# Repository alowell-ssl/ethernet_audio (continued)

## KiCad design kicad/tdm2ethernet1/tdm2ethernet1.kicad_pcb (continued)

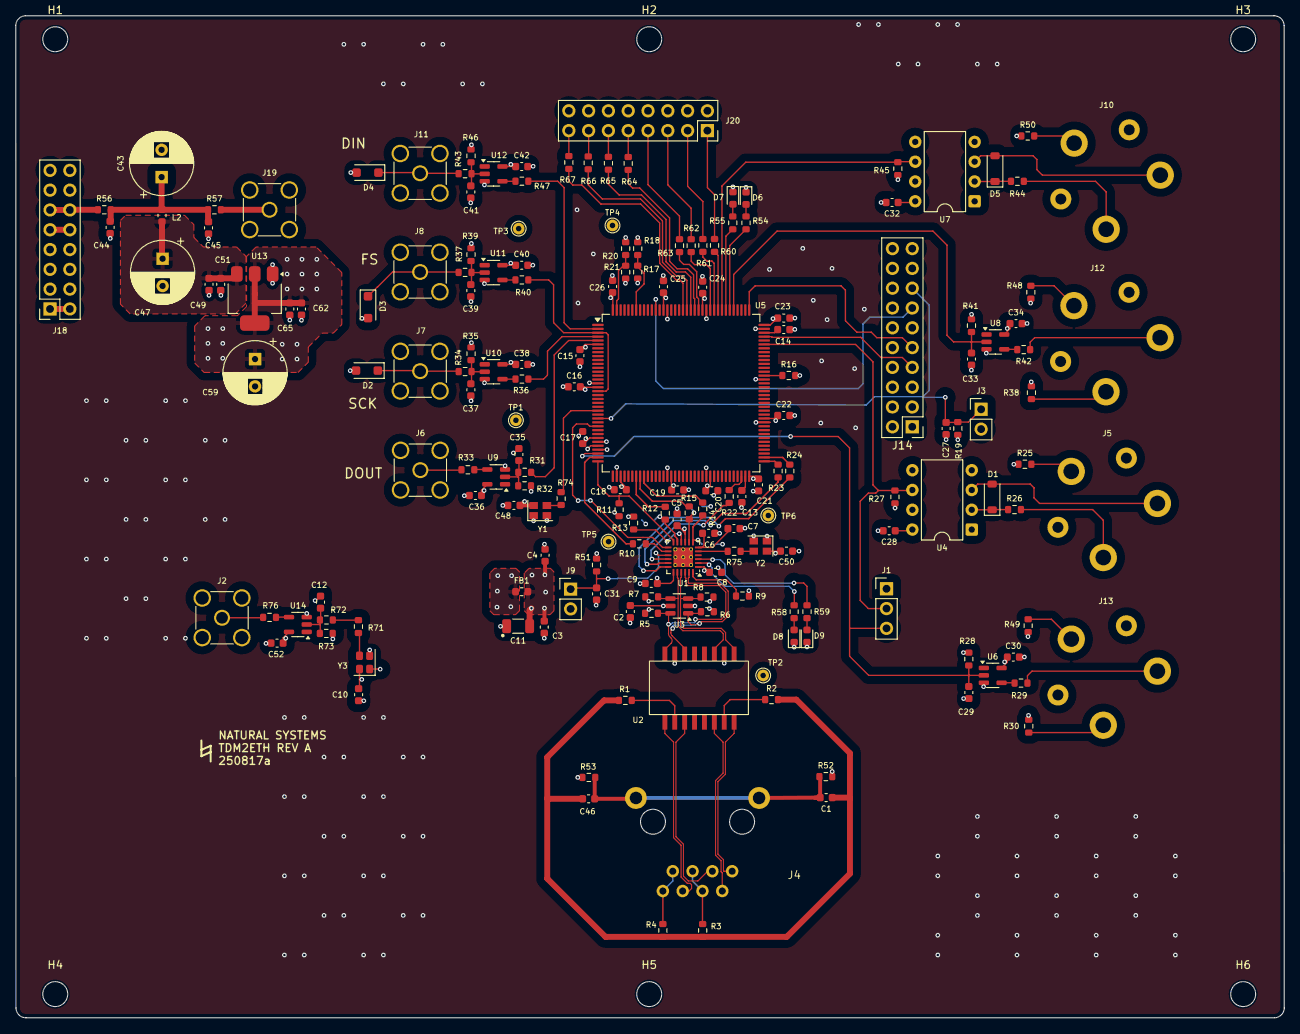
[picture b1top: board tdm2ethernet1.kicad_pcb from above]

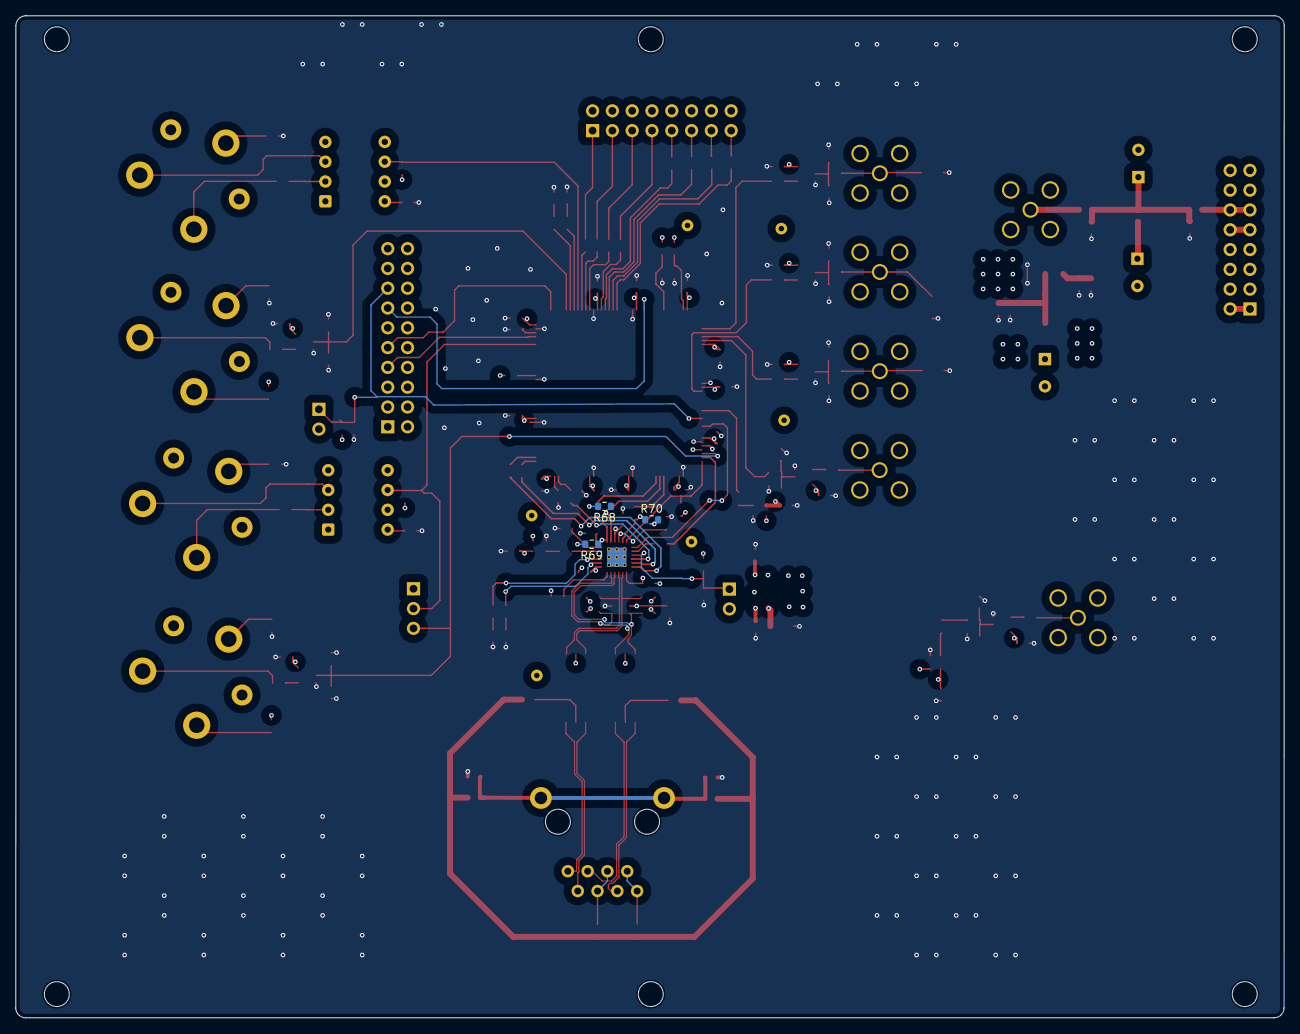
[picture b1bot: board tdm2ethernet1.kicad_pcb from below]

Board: 4 copper layers, 162.7 x 128.5 mm, 188 parts (3 on the bottom side), 121 nets.

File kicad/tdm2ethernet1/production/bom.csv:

Designator,Footprint,Quantity,Value,LCSC Part #
"C1, C46",0603,2,1nF,C1588
"C10, C16, C17, C18, C19, C2, C20, C21, C22, C23, C24, C25, C26, C27, C28, C3, C30, C31, C32, C34, C36, C38, C4, C40, C42, C45, C48, C5, C50, C51, C52, C62, C8, C9",0603,34,100nF,C14663
C11,1206,1,10uF,C13585
"C12, C29, C33, C35, C37, C39, C41",0603,7,C_Small,
"C13, C14",0603,2,2.2uF ceramic low ESR,C23630
"C15, C7",0603,2,1uF,C15849
"C43, C47, C59",CP_Radial_D8.0mm_P3.50mm,3,C_Polarized_Small,
"C44, C49, C65",0603,3,10uF,C96446
C6,0603,1,470pF,C1620
"D1, D5",D_SOD-123,2,1N4148W,C81598
"D2, D3, D4",D_SOD-123F,3,D_Zener_Small,
"D6, D7, D8, D9",0603,4,LED_Small,C2286
FB1,0603,1,600R @ 100 MHz,C1002
J1,PinHeader_1x03_P2.54mm_Vertical,1,Conn_01x03_Pin,
"J10, J12, J13, J5",Amphenol_ACJS,4,ACJS-MV35-3,
"J11, J19, J2, J6, J7, J8",SMA_Amphenol_901-144_Vertical,6,Conn_Coaxial,
J14,PinHeader_2x10_P2.54mm_Vertical,1,Conn_02x10_Odd_Even,
"J18, J20",PinSocket_2x08_P2.54mm_Vertical,2,Conn_02x08_Odd_Even,
"J3, J9",PinHeader_1x02_P2.54mm_Vertical,2,Conn_01x02_Pin,
J4,A-2014-2S-4-N-R,1,8P8C_Shielded,
L2,0603,1,L_Ferrite_Small,C1002
"R1, R2, R3, R4",0603,4,75,C4275
"R10, R12, R14, R15, R22, R23, R24, R29, R42, R71, R74, R75",0603,12,33,C23140
R11,0603,1,1.5k,C22843
"R13, R19, R51, R68, R69, R70",0603,6,10k,C15401
"R16, R17, R18, R20, R21, R25, R31, R34, R37, R43, R48, R49, R50, R52, R53, R56, R57, R60, R61, R62, R63, R64, R65, R66, R67, R72",0603,26,0,C21189
"R26, R44",0603,2,220,C22962
"R27, R45",0603,2,470,C23179
"R28, R32, R35, R39, R41, R46, R73",0603,7,R_Small,
"R30, R38",0603,2,2.2k,C4190
"R33, R36, R40, R47, R76",0603,5,22,C23345
"R5, R6, R7, R8",0603,4,49.9,C23185
"R54, R55, R58, R59",0603,4,4.7k,C23162
R9,0603,1,12.1k,C705723
"TP1, TP2, TP3, TP4, TP5, TP6",TestPoint_THTPad_D1.5mm_Drill0.7mm,6,TestPoint,
U1,VQFN-24-1EP_4x4mm_P0.5mm_EP2.5x2.5mm_ThermalVias,1,LAN8742A,C621424
"U10, U11, U12, U14, U6, U8, U9",SOT-23-5,7,74LVC1G17,C7836
U13,SOT-223,1,TLV1117-33,
U2,Untitled,1,KMS-1102NL,
U3,SOT-23-6,1,USBLC6-4SC6,
"U4, U7",DIP-8_W7.62mm,2,6N137,
U5,LQFP-144_20x20mm_P0.5mm,1,STM32H743ZIT6,C114408
"Y1, Y2",Oscillator_SMD_SeikoEpson_SG210-4Pin_2.5x2.0mm,2,SG-210STF,C70560
Y3,Oscillator_SMD_SeikoEpson_SG210-4Pin_2.5x2.0mm,1,SG-210STF - 24.576 MHz (or Interquip 1651-24575-BTBEYA),C3003263

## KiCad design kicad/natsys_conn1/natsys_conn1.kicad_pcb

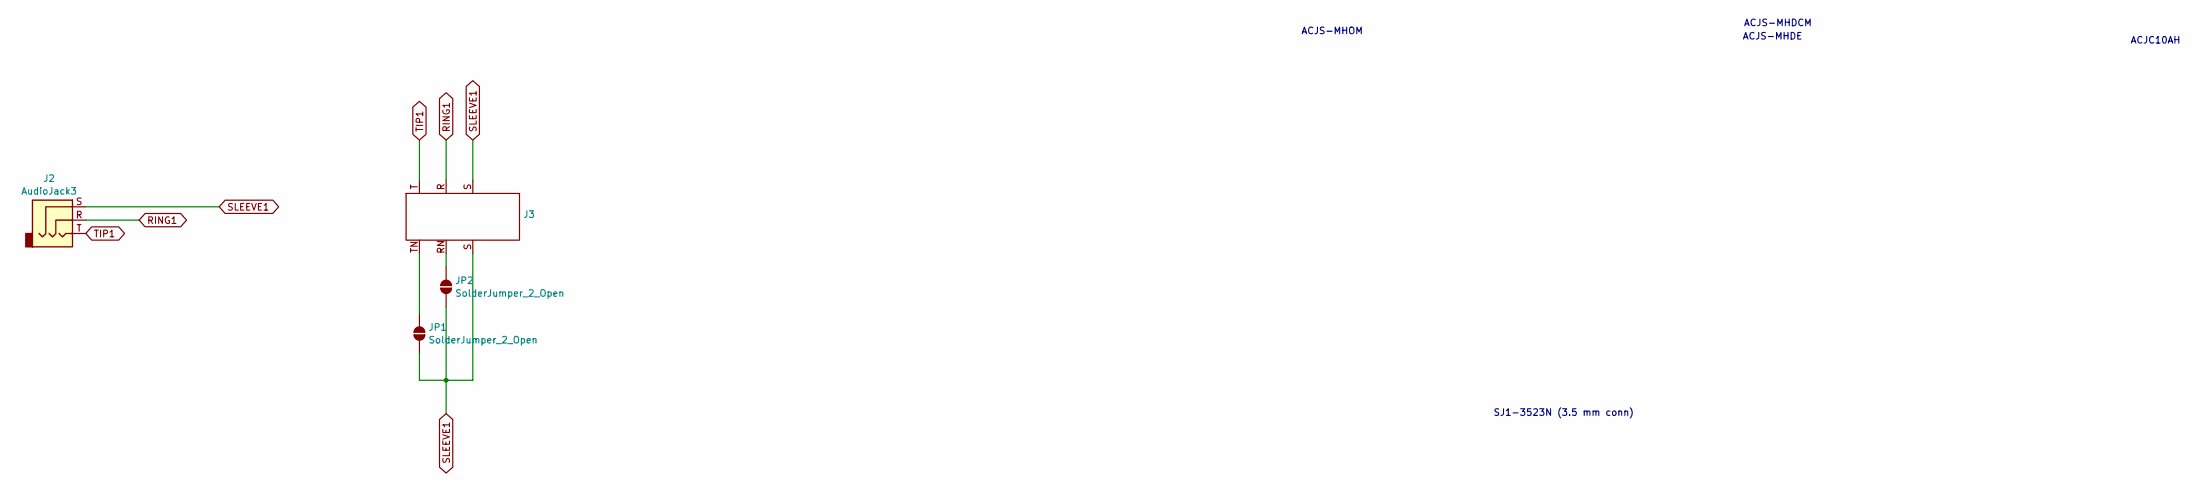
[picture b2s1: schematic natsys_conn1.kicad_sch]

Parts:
J2: AudioJack3; SJ1-3523N
J3: ACJS-MHOM
JP1, JP2: SolderJumper_2_Open; SolderJumper-2_P1.3mm_Open_RoundedPad1.0x1.5mm

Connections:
unnamed: J3.RN, JP2.2 (B)
unnamed: J3.TN, JP1.2 (B)
RING1: J2.R, J3.R
SLEEVE1: J2.S, J3.S, JP1.1 (A), JP2.1 (A)
TIP1: J2.T, J3.T

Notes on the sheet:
SJ1-3523N (3.5 mm conn)
ACJC10AH
ACJS-MHDE
ACJS-MHOM
ACJS-MHDCM

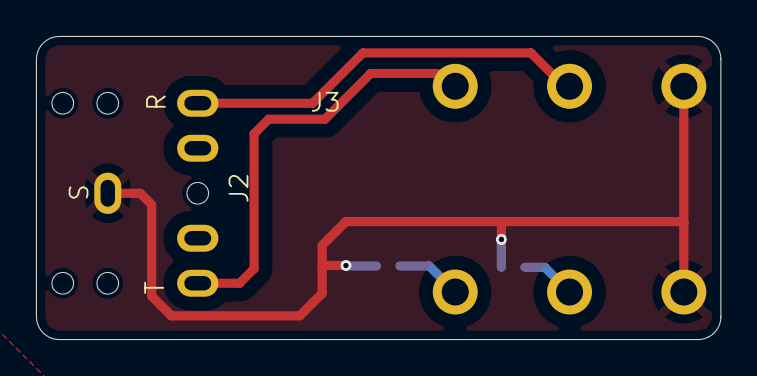
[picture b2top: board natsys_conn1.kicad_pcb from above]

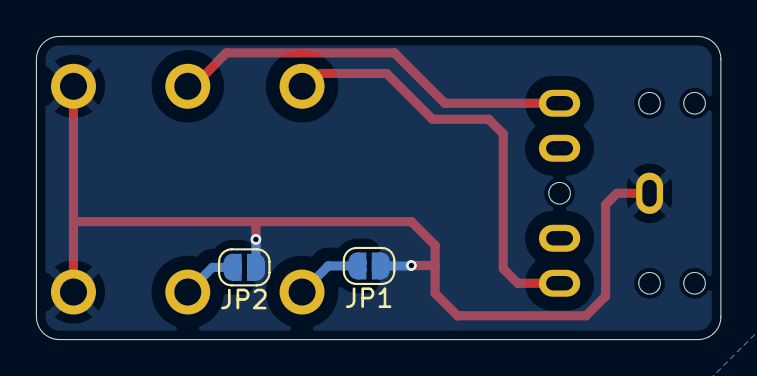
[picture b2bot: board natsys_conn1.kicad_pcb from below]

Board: 2 copper layers, 38.0 x 16.8 mm, 4 parts (2 on the bottom side), 5 nets.

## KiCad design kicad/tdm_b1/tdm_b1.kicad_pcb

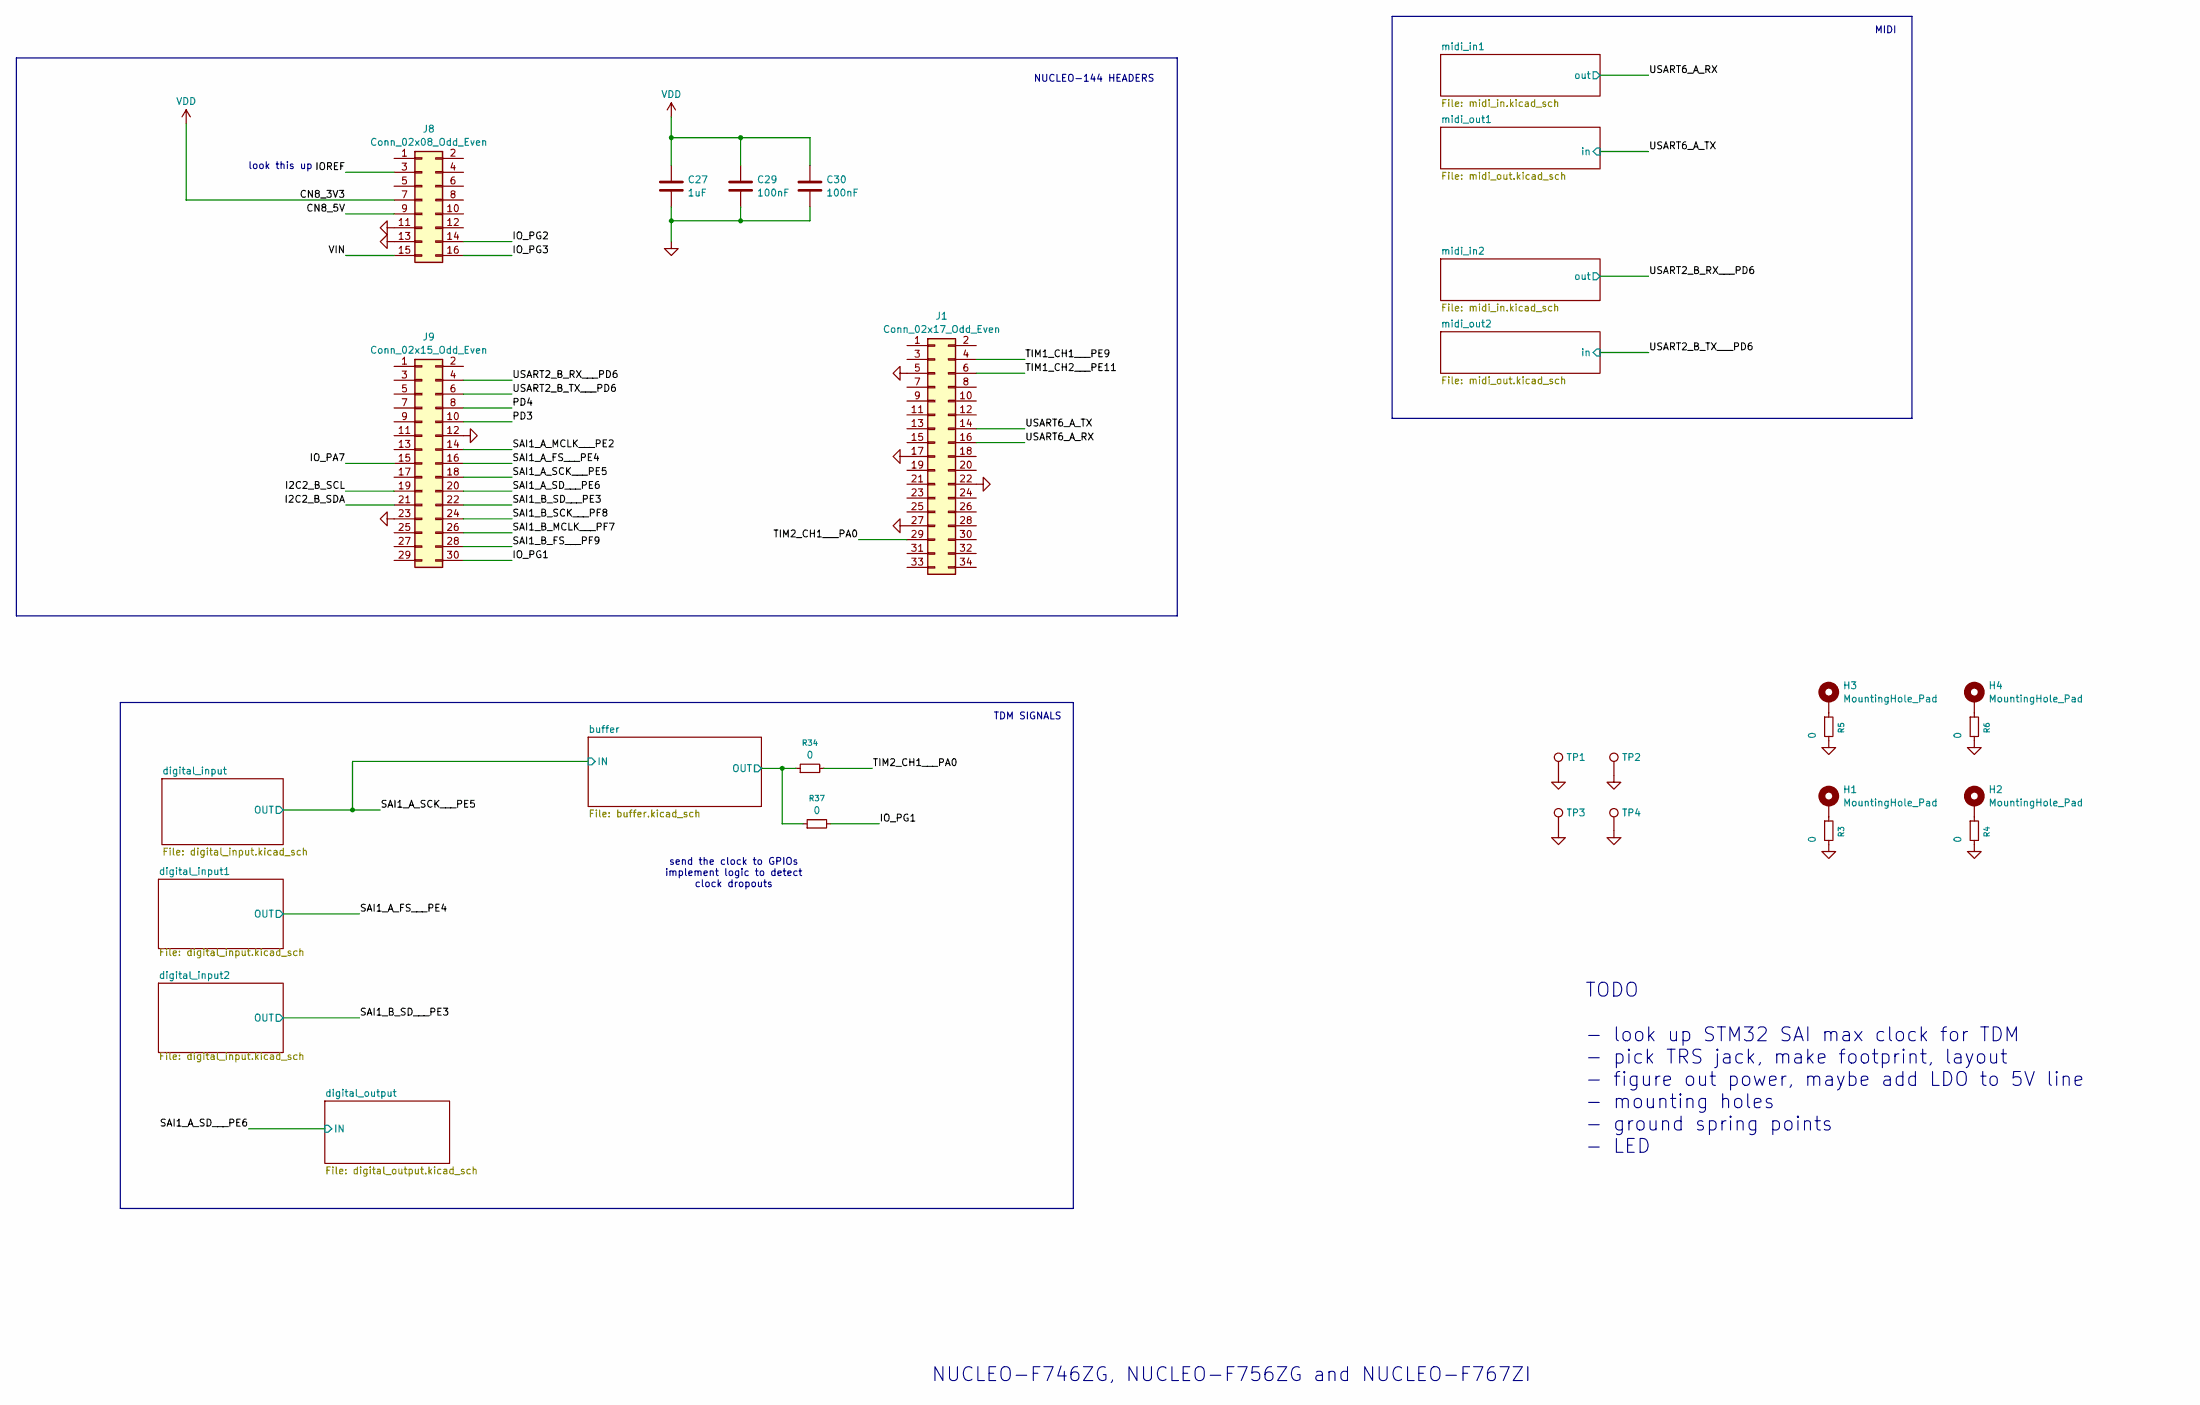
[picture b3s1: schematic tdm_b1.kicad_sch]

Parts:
C27: 1uF; C_0603_1608Metric
C29, C30: 100nF; C_0603_1608Metric
H1, H2, H3, H4: MountingHole_Pad; MountingHole_3.2mm_M3_DIN965_Pad
J1: Conn_02x17_Odd_Even; PinHeader_2x17_P2.54mm_Vertical
J8: Conn_02x08_Odd_Even; PinHeader_2x08_P2.54mm_Vertical
J9: Conn_02x15_Odd_Even; PinHeader_2x15_P2.54mm_Vertical
R3, R4, R5, R6, R34, R37: 0; R_0603_1608Metric
TP1, TP2, TP3, TP4: TestPoint; TestPoint_THTPad_D1.5mm_Drill0.7mm

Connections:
/CN8_5V: J8.9
/I2C2_B_SCL: J9.19
/I2C2_B_SDA: J9.21
/IOREF: J8.3
/IO_PA7: J9.15
/IO_PG1: J9.30, R37.2
/IO_PG2: J8.14
/IO_PG3: J8.16
/PD3: J9.10
/PD4: J9.8
/SAI1_A_FS___PE4: J9.16; also elsewhere on the board
/SAI1_A_MCLK___PE2: J9.14
/SAI1_A_SCK___PE5: J9.18; also elsewhere on the board
/SAI1_A_SD___PE6: J9.20; also elsewhere on the board
/SAI1_B_FS___PF9: J9.28
/SAI1_B_MCLK___PF7: J9.26
/SAI1_B_SCK___PF8: J9.24
/SAI1_B_SD___PE3: J9.22; also elsewhere on the board
/TIM1_CH1___PE9: J1.4
/TIM1_CH2___PE11: J1.6
/TIM2_CH1___PA0: J1.29, R34.2
/USART2_B_RX___PD6: J9.4; also elsewhere on the board
/USART2_B_TX___PD6: J9.6; also elsewhere on the board
/USART6_A_RX: J1.16; also elsewhere on the board
/USART6_A_TX: J1.14; also elsewhere on the board
/VIN: J8.15
/buffer/OUT: R34.1, R37.1; also elsewhere on the board
GND: C27.2, C29.2, C30.2, J1.5, J1.17, J1.22, J1.27, J8.11, J8.13, J9.12, J9.23, R3.2, R4.2, R5.2, R6.2, TP1.1, TP2.1, TP3.1, TP4.1; also elsewhere on the board
unnamed: H1.1, R3.1
unnamed: H2.1, R4.1
unnamed: H3.1, R5.1
unnamed: H4.1, R6.1
VDD: C27.1, C29.1, C30.1, J8.7; also elsewhere on the board

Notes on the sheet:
TDM SIGNALS
TODO - look up STM32 SAI max clock for TDM - pick TRS jack, make footprint, layout - figure out power, maybe add LDO to 5V line - mounting holes - ground spring points - LED
NUCLEO-144 HEADERS
look this up
send the clock to GPIOs implement logic to detect clock dropouts
NUCLEO-F746ZG, NUCLEO-F756ZG and NUCLEO-F767ZI
MIDI

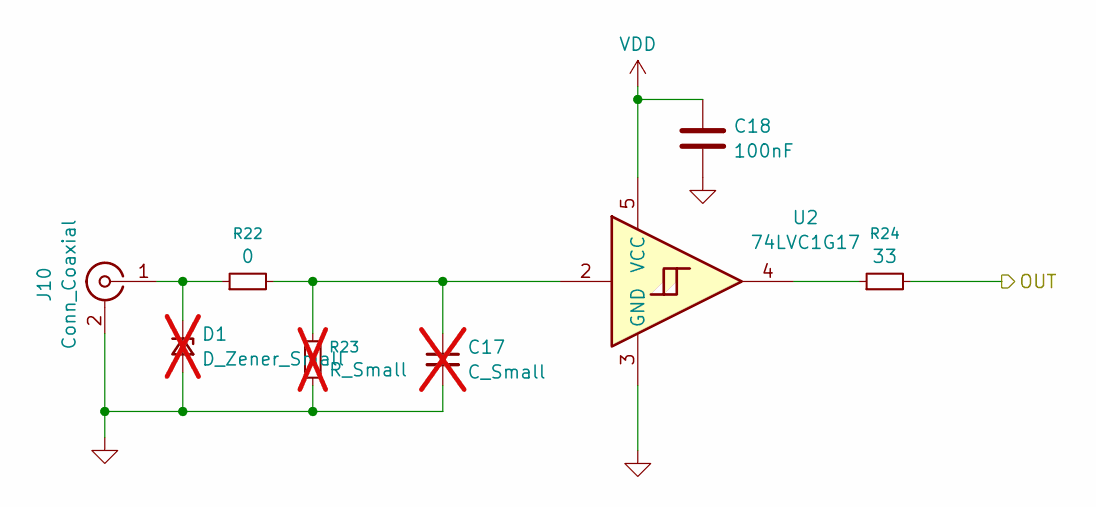
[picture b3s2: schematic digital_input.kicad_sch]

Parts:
C17: C_Small; C_0603_1608Metric; not fitted
C18: 100nF; C_0603_1608Metric
D1: D_Zener_Small; D_SOD-123F; not fitted
J10: Conn_Coaxial; SMA_Amphenol_901-144_Vertical
R22: 0; R_0603_1608Metric
R23: R_Small; R_0603_1608Metric; not fitted
R24: 33; R_0603_1608Metric
U2: 74LVC1G17; SOT-23-5

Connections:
/SAI1_A_SCK___PE5: R24.2; also elsewhere on the board
GND: C17.2, C18.2, D1.2 (A), J10.2 (Ext), R23.1, U2.3 (GND); also elsewhere on the board
unnamed: C17.1, R22.2, R23.2, U2.2
unnamed: D1.1 (K), J10.1 (In), R22.1
unnamed: R24.1, U2.4
VDD: C18.1, U2.5 (VCC); also elsewhere on the board

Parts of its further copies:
C19, C21: C_Small; C_0603_1608Metric; not fitted
C20, C22: 100nF; C_0603_1608Metric
D2, D3: D_Zener_Small; D_SOD-123F; not fitted
J11, J13: Conn_Coaxial; SMA_Amphenol_901-144_Vertical
R25, R28: 0; R_0603_1608Metric
R26, R29: R_Small; R_0603_1608Metric; not fitted
R27, R30: 33; R_0603_1608Metric
U3, U4: 74LVC1G17; SOT-23-5

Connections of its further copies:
/SAI1_A_FS___PE4: R27.2; also elsewhere on the board
/SAI1_B_SD___PE3: R30.2; also elsewhere on the board
GND: C19.2, C20.2, C21.2, C22.2, D2.2 (A), D3.2 (A), J11.2 (Ext), J13.2 (Ext), R26.1, R29.1, U3.3 (GND), U4.3 (GND); also elsewhere on the board
unnamed: C19.1, R25.2, R26.2, U3.2
unnamed: C21.1, R28.2, R29.2, U4.2
unnamed: D2.1 (K), J11.1 (In), R25.1
unnamed: D3.1 (K), J13.1 (In), R28.1
unnamed: R27.1, U3.4
unnamed: R30.1, U4.4
VDD: C20.1, C22.1, U3.5 (VCC), U4.5 (VCC); also elsewhere on the board

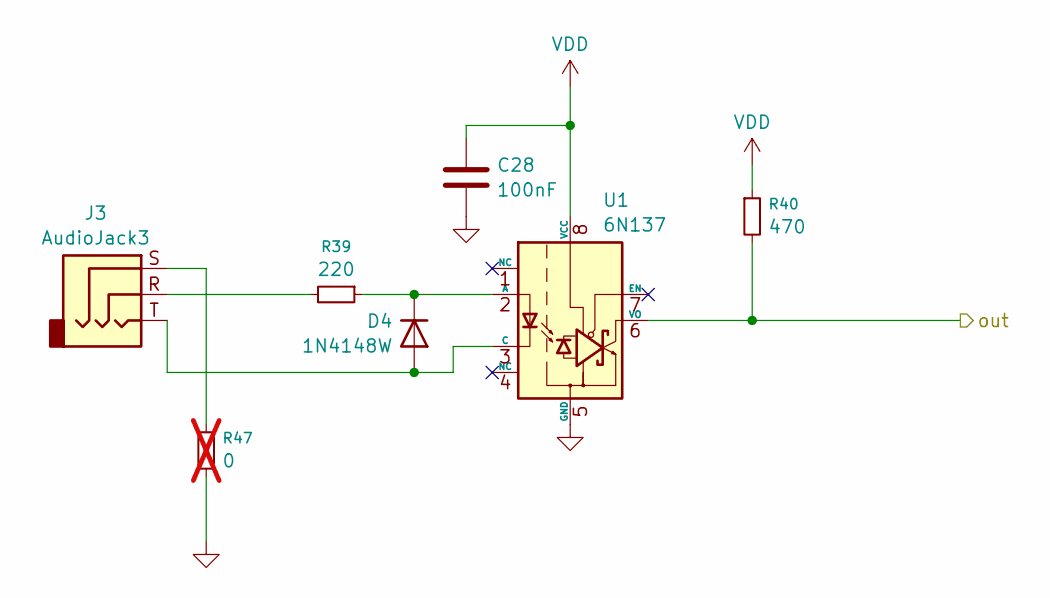
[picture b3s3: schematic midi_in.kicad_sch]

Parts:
C28: 100nF; C_0603_1608Metric
D4: 1N4148W; D_SOD-123
J3: AudioJack3; SJ1-3523N
R39: 220; R_0603_1608Metric
R40: 470; R_0603_1608Metric
R47: 0; R_0603_1608Metric; not fitted
U1: 6N137; DIP-8_W7.62mm

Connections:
/USART6_A_RX: R40.2, U1.6 (VO); also elsewhere on the board
GND: C28.2, R47.1, U1.5 (GND); also elsewhere on the board
unnamed: D4.2 (A), J3.T, U1.3 (C)
unnamed: D4.1 (K), R39.1, U1.2 (A)
unnamed: J3.R, R39.2
unnamed: J3.S, R47.2
VDD: C28.1, R40.1, U1.8 (VCC); also elsewhere on the board

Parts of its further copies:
C33: 100nF; C_0603_1608Metric
D5: 1N4148W; D_SOD-123
J5: AudioJack3; SJ1-3523N
R44: 220; R_0603_1608Metric
R45: 470; R_0603_1608Metric
R50: 0; R_0603_1608Metric; not fitted
U8: 6N137; DIP-8_W7.62mm

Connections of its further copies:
/USART2_B_RX___PD6: R45.2, U8.6 (VO); also elsewhere on the board
GND: C33.2, R50.1, U8.5 (GND); also elsewhere on the board
unnamed: D5.2 (A), J5.T, U8.3 (C)
unnamed: D5.1 (K), R44.1, U8.2 (A)
unnamed: J5.R, R44.2
unnamed: J5.S, R50.2
VDD: C33.1, R45.1, U8.8 (VCC); also elsewhere on the board

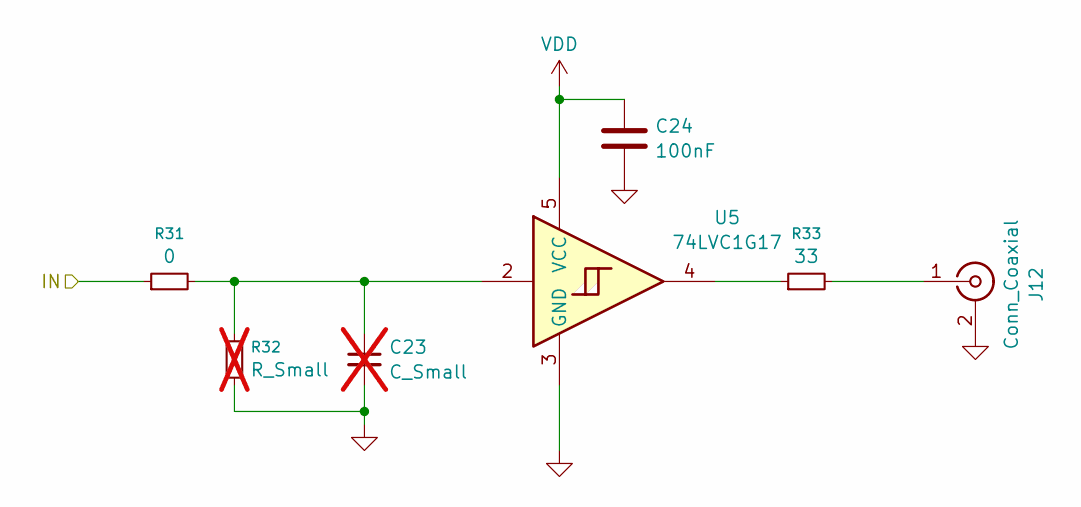
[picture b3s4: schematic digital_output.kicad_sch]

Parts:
C23: C_Small; C_0603_1608Metric; not fitted
C24: 100nF; C_0603_1608Metric
J12: Conn_Coaxial; SMA_Amphenol_901-144_Vertical
R31: 0; R_0603_1608Metric
R32: R_Small; R_0603_1608Metric; not fitted
R33: 33; R_0603_1608Metric
U5: 74LVC1G17; SOT-23-5

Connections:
/SAI1_A_SD___PE6: R31.1; also elsewhere on the board
GND: C23.2, C24.2, J12.2 (Ext), R32.1, U5.3 (GND); also elsewhere on the board
unnamed: C23.1, R31.2, R32.2, U5.2
unnamed: J12.1 (In), R33.2
unnamed: R33.1, U5.4
VDD: C24.1, U5.5 (VCC); also elsewhere on the board

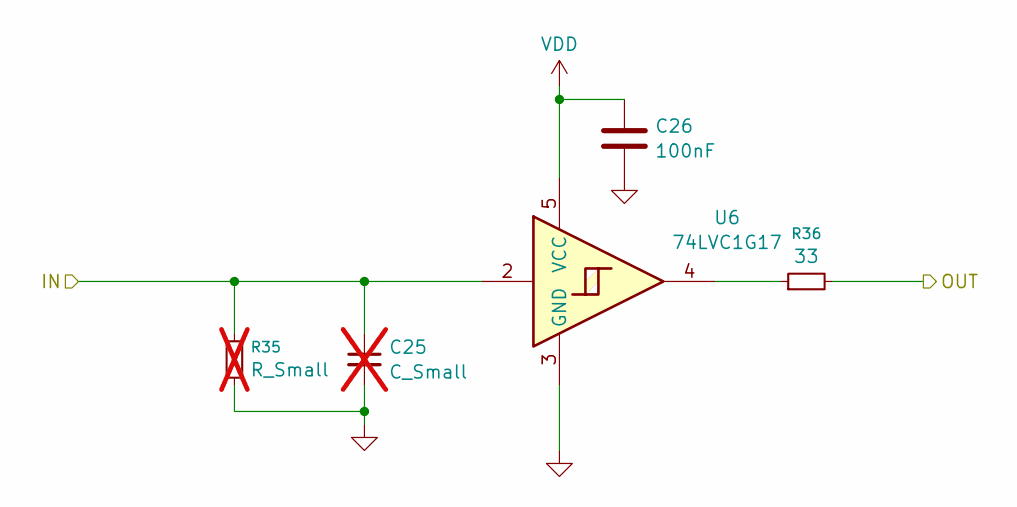
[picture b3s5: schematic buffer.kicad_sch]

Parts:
C25: C_Small; C_0603_1608Metric; not fitted
C26: 100nF; C_0603_1608Metric
R35: R_Small; R_0603_1608Metric; not fitted
R36: 33; R_0603_1608Metric
U6: 74LVC1G17; SOT-23-5

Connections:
/SAI1_A_SCK___PE5: C25.1, R35.2, U6.2; also elsewhere on the board
/buffer/OUT: R36.2; also elsewhere on the board
GND: C25.2, C26.2, R35.1, U6.3 (GND); also elsewhere on the board
unnamed: R36.1, U6.4
VDD: C26.1, U6.5 (VCC); also elsewhere on the board

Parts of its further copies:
C31, C34: C_Small; C_0603_1608Metric; not fitted
C32, C35: 100nF; C_0603_1608Metric
R41, R46: R_Small; R_0603_1608Metric; not fitted
R42, R51: 33; R_0603_1608Metric
U7, U9: 74LVC1G17; SOT-23-5

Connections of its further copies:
/USART2_B_TX___PD6: C34.1, R46.2, U9.2; also elsewhere on the board
/USART6_A_TX: C31.1, R41.2, U7.2; also elsewhere on the board
/midi_out1/MIDI_OUT: R42.2; also elsewhere on the board
/midi_out2/MIDI_OUT: R51.2; also elsewhere on the board
GND: C31.2, C32.2, C34.2, C35.2, R41.1, R46.1, U7.3 (GND), U9.3 (GND); also elsewhere on the board
unnamed: R42.1, U7.4
unnamed: R51.1, U9.4
VDD: C32.1, C35.1, U7.5 (VCC), U9.5 (VCC); also elsewhere on the board

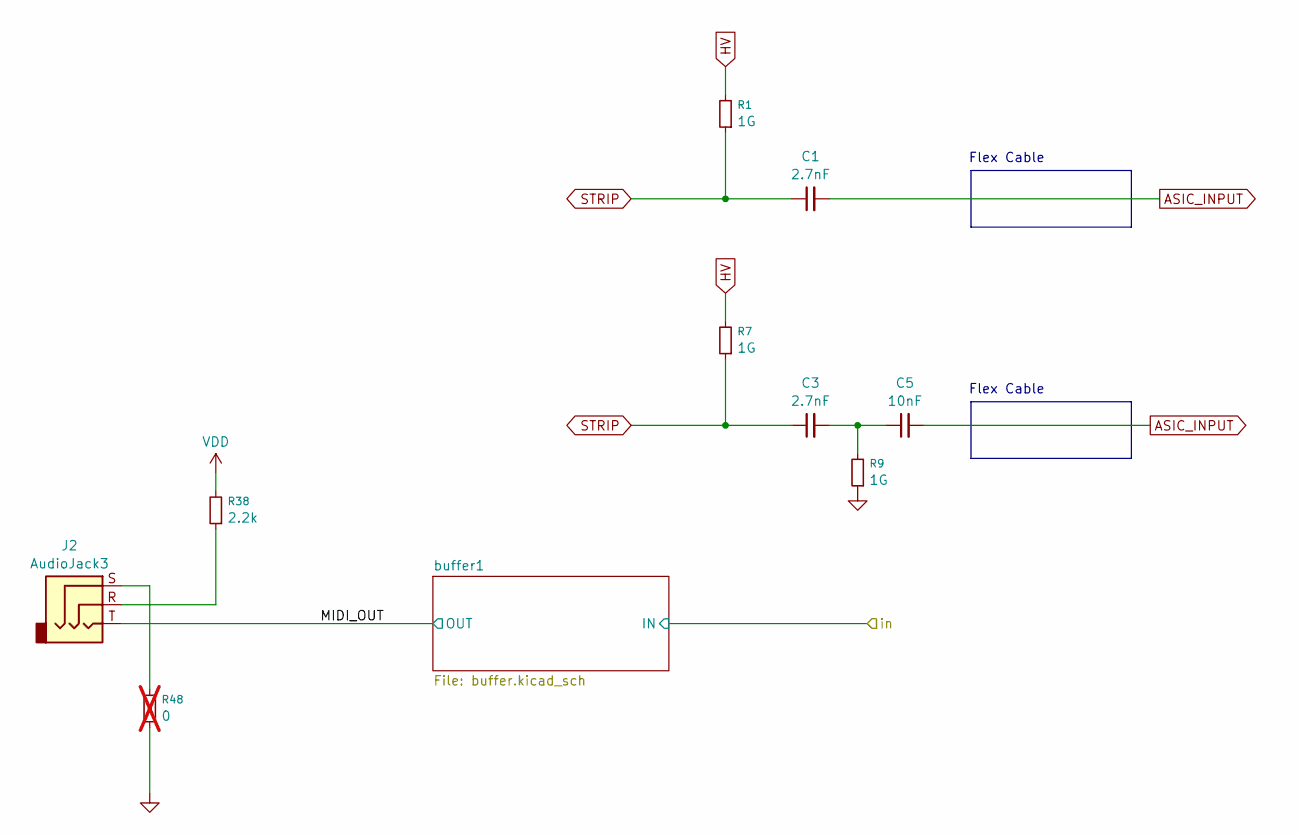
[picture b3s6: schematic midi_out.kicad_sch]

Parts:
C1, C3: 2.7nF
C5: 10nF
J2: AudioJack3; SJ1-3523N
R1, R7, R9: 1G; R_0603_1608Metric
R38: 2.2k; R_0603_1608Metric
R48: 0; R_0603_1608Metric; not fitted

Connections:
/midi_out1/MIDI_OUT: J2.T; also elsewhere on the board
GND: R9.1, R48.1; also elsewhere on the board
unnamed: C1.1, C3.1, R1.1, R7.1
unnamed: C1.2, C5.2
unnamed: C3.2, C5.1, R9.2
unnamed: J2.R, R38.1
unnamed: J2.S, R48.2
unnamed: R1.2, R7.2
VDD: R38.2; also elsewhere on the board

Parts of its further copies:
J4: AudioJack3; SJ1-3523N
R43: 2.2k; R_0603_1608Metric
R49: 0; R_0603_1608Metric; not fitted

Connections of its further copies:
/midi_out2/MIDI_OUT: J4.T; also elsewhere on the board
GND: R49.1; also elsewhere on the board
unnamed: J4.R, R43.1
unnamed: J4.S, R49.2
VDD: R43.2; also elsewhere on the board

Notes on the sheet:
Flex Cable

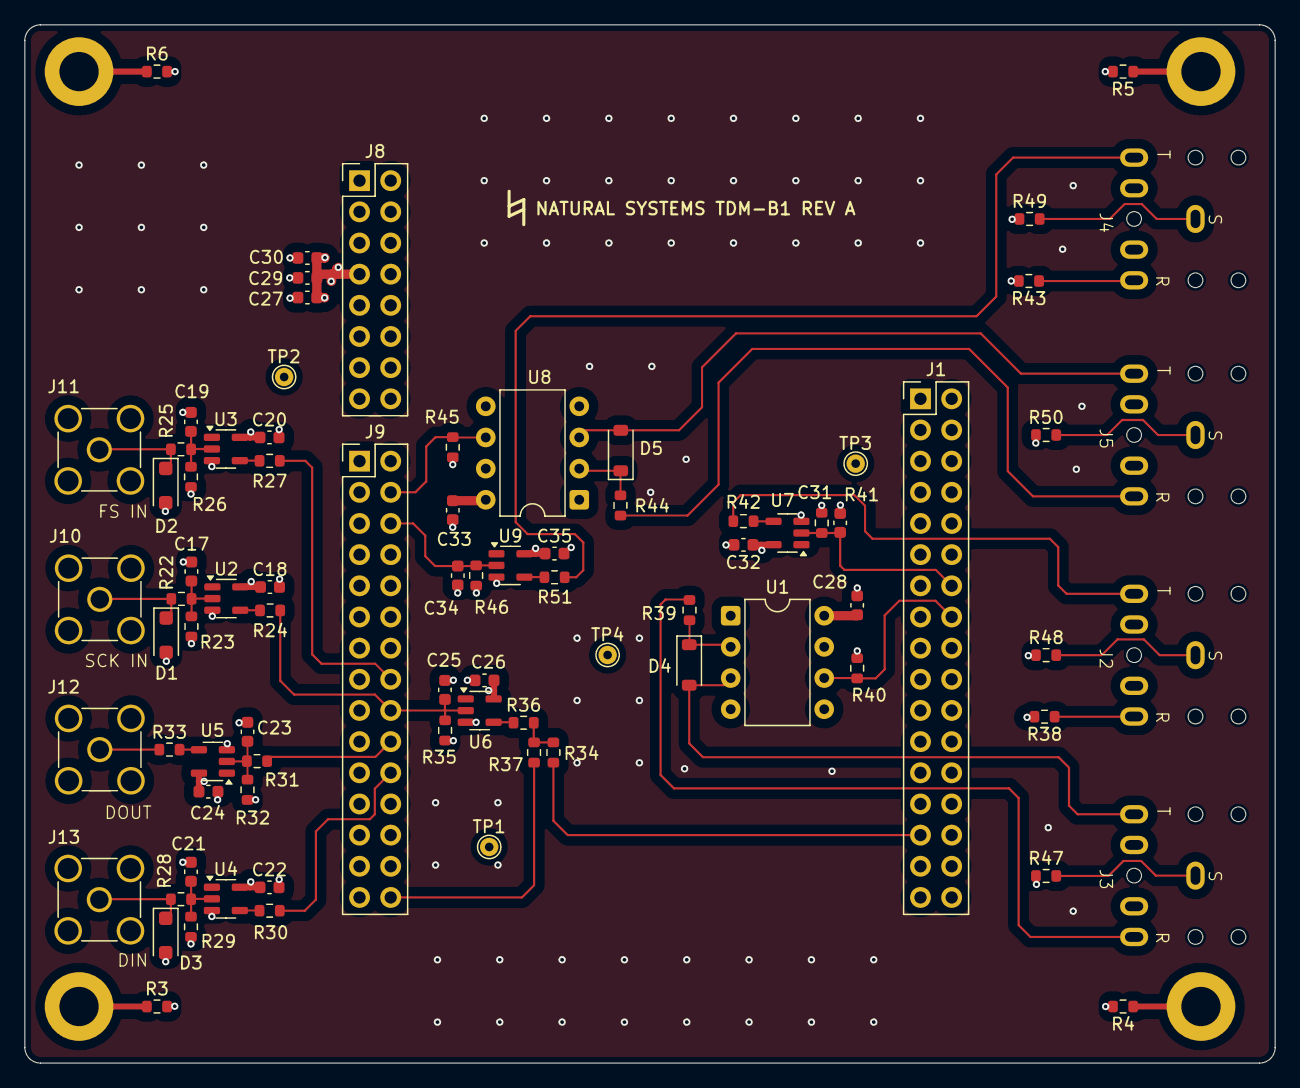
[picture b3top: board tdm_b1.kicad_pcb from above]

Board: 4 copper layers, 101.9 x 84.6 mm, 86 parts (0 on the bottom side), 46 nets.

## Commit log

2025-10-06 Adding files
